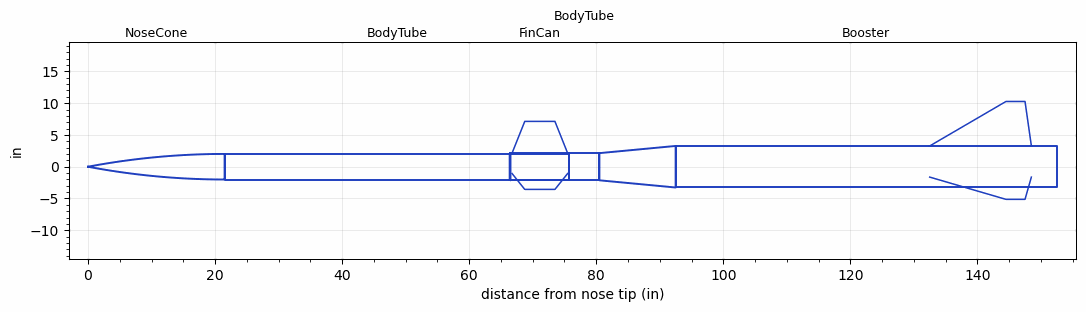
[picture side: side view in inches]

<RASAeroDocument>
 <FileVersion>2</FileVersion>
 <RocketDesign>
  <NoseCone>
   <Length>21.5</Length>
   <Diameter>4.026</Diameter>
   <Shape>Tangent Ogive</Shape>
   <BluntRadius>0.125</BluntRadius>
   <Location>0</Location>
  </NoseCone>
  <BodyTube>
   <Length>54.25</Length>
   <Diameter>4.026</Diameter>
   <Location>21.5</Location>
  </BodyTube>
  <FinCan>
   <Length>9.25</Length>
   <Diameter>4.276</Diameter>
   <InsideDiameter>4.026</InsideDiameter>
   <Location>75.75</Location>
   <ShoulderLength>0.125</ShoulderLength>
   <Offset>-9.25</Offset>
   <Fin>
    <Count>3</Count>
    <Chord>8.75</Chord>
    <Span>5</Span>
    <SweepDistance>2</SweepDistance>
    <TipChord>4.75</TipChord>
    <Thickness>0.125</Thickness>
    <LERadius>0.0625</LERadius>
    <Location>9</Location>
    <AirfoilSection>Hexagonal</AirfoilSection>
    <FX1>0.5</FX1>
    <FX3>0.5</FX3>
   </Fin>
  </FinCan>
  <BodyTube>
   <Length>4.75</Length>
   <Diameter>4.276</Diameter>
   <Location>75.75</Location>
  </BodyTube>
  <Booster>
   <Length>60</Length>
   <Diameter>6.54</Diameter>
   <InsideDiameter>4.276</InsideDiameter>
   <Location>80.5</Location>
   <ShoulderLength>12</ShoulderLength>
   <Fin>
    <Count>3</Count>
    <Chord>16</Chord>
    <Span>7</Span>
    <SweepDistance>12</SweepDistance>
    <TipChord>3</TipChord>
    <Thickness>0.1875</Thickness>
    <LERadius>0.0313</LERadius>
    <Location>20</Location>
    <AirfoilSection>Hexagonal</AirfoilSection>
    <FX1>0.992</FX1>
    <FX3>0.544</FX3>
   </Fin>
  </Booster>
  <Surface>Rough Camouflage Paint</Surface>
  <ModifiedBarrowman>True</ModifiedBarrowman>
  <Turbulence>True</Turbulence>
  <UseBooster1>False</UseBooster1>
  <UseBooster2>False</UseBooster2>
 </RocketDesign>
 <LaunchSite>
  <Altitude>50</Altitude>
  <Pressure>0</Pressure>
  <RodAngle>1</RodAngle>
  <RodLength>19</RodLength>
  <Temperature>70</Temperature>
  <WindSpeed>10</WindSpeed>
 </LaunchSite>
 <Recovery>
  <Altitude1>1000</Altitude1>
  <Altitude2>1000</Altitude2>
  <DeviceType1>None</DeviceType1>
  <DeviceType2>None</DeviceType2>
  <Event1>False</Event1>
  <Event2>False</Event2>
  <Size1>1</Size1>
  <Size2>1</Size2>
  <EventType1>None</EventType1>
  <EventType2>None</EventType2>
  <CD1>1.33</CD1>
  <CD2>1.33</CD2>
 </Recovery>
 <SimulationList>
  <Simulation>
   <SustainerEngine>K735-SK-P  (CTI)</SustainerEngine>
   <SustainerLaunchWt>26.5</SustainerLaunchWt>
   <SustainerNozzleDiameter>2.75</SustainerNozzleDiameter>
   <SustainerCG>55</SustainerCG>
   <SustainerIgnitionDelay>2</SustainerIgnitionDelay>
   <Booster1Engine>M3400-WT  (CTI)</Booster1Engine>
   <Booster1LaunchWt>83</Booster1LaunchWt>
   <Booster1SeparationDelay>0.5</Booster1SeparationDelay>
   <Booster1IgnitionDelay>0</Booster1IgnitionDelay>
   <Booster1CG>100</Booster1CG>
   <Booster1NozzleDiameter>3.625</Booster1NozzleDiameter>
   <IncludeBooster1>True</IncludeBooster1>
   <Booster2Delay>0</Booster2Delay>
   <IncludeBooster2>True</IncludeBooster2>
   <TimetoApogee>30.84053</TimetoApogee>
   <MaxAltitude>14965.24</MaxAltitude>
   <MaxVelocity>1053.185</MaxVelocity>
  </Simulation>
  <Simulation>
   <SustainerEngine>K735-SK-P  (CTI)</SustainerEngine>
   <SustainerLaunchWt>26.5</SustainerLaunchWt>
   <SustainerNozzleDiameter>2.75</SustainerNozzleDiameter>
   <SustainerCG>55</SustainerCG>
   <SustainerIgnitionDelay>2</SustainerIgnitionDelay>
   <Booster1Engine>M2505  (CTI)</Booster1Engine>
   <Booster1LaunchWt>79</Booster1LaunchWt>
   <Booster1SeparationDelay>0.5</Booster1SeparationDelay>
   <Booster1IgnitionDelay>0</Booster1IgnitionDelay>
   <Booster1CG>98</Booster1CG>
   <Booster1NozzleDiameter>3.625</Booster1NozzleDiameter>
   <IncludeBooster1>True</IncludeBooster1>
   <Booster2Delay>0</Booster2Delay>
   <IncludeBooster2>False</IncludeBooster2>
   <TimetoApogee>28.84048</TimetoApogee>
   <MaxAltitude>11937.63</MaxAltitude>
   <MaxVelocity>909.8261</MaxVelocity>
  </Simulation>
  <Simulation>
   <SustainerEngine>K510  (CTI)</SustainerEngine>
   <SustainerLaunchWt>26.5</SustainerLaunchWt>
   <SustainerNozzleDiameter>2.75</SustainerNozzleDiameter>
   <SustainerCG>55</SustainerCG>
   <SustainerIgnitionDelay>2</SustainerIgnitionDelay>
   <Booster1Engine>M2505  (CTI)</Booster1Engine>
   <Booster1LaunchWt>79</Booster1LaunchWt>
   <Booster1SeparationDelay>0.5</Booster1SeparationDelay>
   <Booster1IgnitionDelay>0</Booster1IgnitionDelay>
   <Booster1CG>98</Booster1CG>
   <Booster1NozzleDiameter>3.625</Booster1NozzleDiameter>
   <IncludeBooster1>True</IncludeBooster1>
   <Booster2Delay>0</Booster2Delay>
   <IncludeBooster2>False</IncludeBooster2>
   <TimetoApogee>31.71055</TimetoApogee>
   <MaxAltitude>14267.37</MaxAltitude>
   <MaxVelocity>950.0467</MaxVelocity>
  </Simulation>
  <Simulation>
   <SustainerEngine>K510  (CTI)</SustainerEngine>
   <SustainerLaunchWt>26.5</SustainerLaunchWt>
   <SustainerNozzleDiameter>2.75</SustainerNozzleDiameter>
   <SustainerCG>55</SustainerCG>
   <SustainerIgnitionDelay>2</SustainerIgnitionDelay>
   <Booster1Engine>M3400-WT  (CTI)</Booster1Engine>
   <Booster1LaunchWt>83</Booster1LaunchWt>
   <Booster1SeparationDelay>0.5</Booster1SeparationDelay>
   <Booster1IgnitionDelay>0</Booster1IgnitionDelay>
   <Booster1CG>100</Booster1CG>
   <Booster1NozzleDiameter>3.625</Booster1NozzleDiameter>
   <IncludeBooster1>True</IncludeBooster1>
   <Booster2Delay>0</Booster2Delay>
   <IncludeBooster2>False</IncludeBooster2>
   <TimetoApogee>33.38058</TimetoApogee>
   <MaxAltitude>17268.15</MaxAltitude>
   <MaxVelocity>1062.219</MaxVelocity>
  </Simulation>
  <Simulation>
   <SustainerEngine>K735-SK-P  (CTI)</SustainerEngine>
   <SustainerLaunchWt>26.5</SustainerLaunchWt>
   <SustainerNozzleDiameter>2.75</SustainerNozzleDiameter>
   <SustainerCG>55</SustainerCG>
   <SustainerIgnitionDelay>1.5</SustainerIgnitionDelay>
   <Booster1Engine>M2505  (CTI)</Booster1Engine>
   <Booster1LaunchWt>79</Booster1LaunchWt>
   <Booster1SeparationDelay>0.5</Booster1SeparationDelay>
   <Booster1IgnitionDelay>0</Booster1IgnitionDelay>
   <Booster1CG>98</Booster1CG>
   <Booster1NozzleDiameter>3.625</Booster1NozzleDiameter>
   <IncludeBooster1>True</IncludeBooster1>
   <Booster2Delay>0</Booster2Delay>
   <IncludeBooster2>False</IncludeBooster2>
   <TimetoApogee>28.53047</TimetoApogee>
   <MaxAltitude>11926.27</MaxAltitude>
   <MaxVelocity>926.0245</MaxVelocity>
  </Simulation>
 </SimulationList>
</RASAeroDocument>
